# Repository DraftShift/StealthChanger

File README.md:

#  StealthChanger
**Tool changing system for Vorons and other front mount printer motion systems.**

&nbsp;&nbsp;&nbsp;&nbsp;&nbsp;&nbsp;
<a href="https://github.com/sponsors/DraftShift" target="_blank" alt="Sponsor Us">&color=rgb(191%2C%2057%2C%20137))</a>

 ## 🌐 Official Website

StealthChanger now has an official website!

👉 **https://stealthchanger.com** 

##

## Introduction

Unlike the name suggests we support more then just stealthburner.

Due to difficulties with heat insert and aligning of bearings and mounts we wanted to try a more simplistic design based on bushings and pins.

This is a very light design, requiring less parts and as such is cheaper and easier to build.  Input shaper tests have shown it to be as rigid if not more than current Tapchanger.

All parts are easily replaceable without reprinting if wear happens, life of the bushings and pins are still being tested.

## Tool compatability
Currently we support the standard Stealth Burner, Dragon Burner, Rapid Burner, Yavoth, AntHead, A4T, XOL, Jabberwocky and Archetype BlackBird.  There is also a usermod for the [Mini Stealth Burner](UserMods/jdmontgomer/MiniSB_SC).

## V1.1 Release
The original StealthChanger shuttle and backplates have been updated to V1.1, this update is to improve rigidity and probe accuracy. To help identify the version, "V1.1" has been clearly marked on all shuttles and backplates. please note, V1.1 is NOT compatible with previous versions. Updated documentation will follow shorly.

## Documentation and Info

Please use our [wiki](../../wiki) for more information and documentation.

- [Bill of Materials](../../wiki/Bill-of-Materials)
- [Docks](../../wiki/Docks)
- [Printing](../../wiki/Printing)
- [Assembling](../../wiki/Assembling)
- [Installation](../../wiki/Installation)
- [Configuration](../../wiki/Configuration)
- [Calibration](../../wiki/Calibration)
- [Slicers](../../wiki/Slicers)
- [Serials](../../wiki/Serials)
- [Support and FAQs](../../wiki/Support-and-FAQs)
- [Contributing & Donating](../../wiki/Contributing-and-Donating)
- [Team & Credits](../../wiki/Team-and-Credits)
- [Vendors & Kits](../../wiki/Vendors-and-Kits)

## Preview
### Explaination Video featuring GMBridge

### Printed Parts (Dragonburner) by BT123

### Important! - Check for clear Hex's (Dragonburner) by BT123

### Assembled Shuttle and Backplate by BT123

### Motion (Stealthburner) by TheSin-

### Docking (Stealthburner) by fiferboy

Originally based on Viesturz's [Tapchanger](https://github.com/viesturz/tapchanger)

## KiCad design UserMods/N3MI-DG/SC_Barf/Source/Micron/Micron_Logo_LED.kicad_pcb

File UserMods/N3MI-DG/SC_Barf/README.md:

# SC Barf LEDs

PCBs with 1.5mm RGB LEDs arranged into the StealthChanger logo pattern, both Voron and Micron styles.

## Example Config

```text
[neopixel rgb_logo]
pin: PB3
color_order: GRB
chain_count: 21 # 21 for Voron style, 19 for Micron style.
initial_RED: 0.3
initial_BLUE: 0.0
initial_GREEN: 0.3
```

## How to Order from JLCPCB

- Add Gerber zip file
- Select the PCB qty you want
- Select the PCB color you want
- Select `Order Number(Specify Position)`
- Enable PCB Assembly
- Select `Added by Customer` in the Tooling holes section
- Press the `Next` button
- Press the next `Next` button
- Add BOM file `BOM-JLC.csv`
- Add CPL file `CPL-JLC.csv`
- Click the `Process BOM & CPL` button
- Make sure the selected componants are correct
- Click the `Next` button
- Confirm componant placement
- Click the `Next` button
- Save to cart & checkout.

Note. there is an alternative RGB led componant that can be selected if the `SK6805-EC15` is out of stock. `DY-S1515065/RGBC/6805-5T` by TONYU is 1:1 compatible but the JLC footprint is rotated 180 degrees. Confirm you have the correct orientations.

### SK6805-EC15

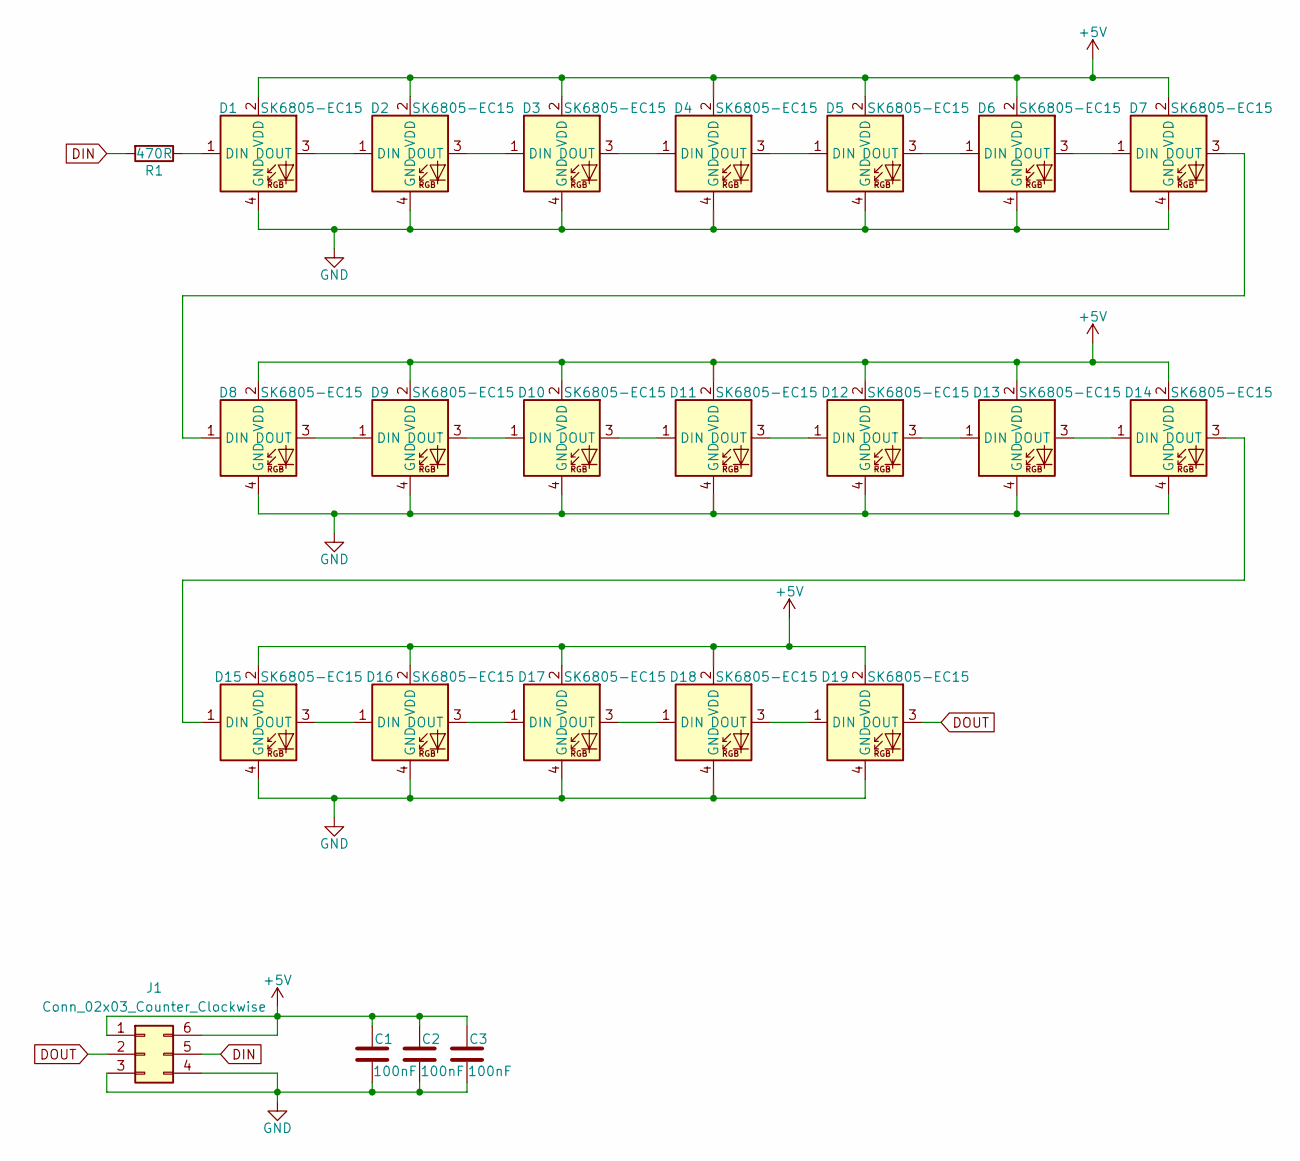
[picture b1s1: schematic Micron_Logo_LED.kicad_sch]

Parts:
C1, C2, C3: 100nF; C_0402_1005Metric; LCSC C14445
D1, D2, D3, D4, D5, D6, D7, D8, D9, D10, D11, D12, D13, D14, D15, D16, D17, D18, D19: SK6805-EC15; LCSC C2890035
J1: Conn_02x03_Counter_Clockwise; PinHeader_2x03_P2.54mm_Vertical_SMD
R1: 470R; R_0402_1005Metric; LCSC C25117

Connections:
+5V: C1.2, C2.2, C3.2, D1.2 (VDD), D2.2 (VDD), D3.2 (VDD), D4.2 (VDD), D5.2 (VDD), D6.2 (VDD), D7.2 (VDD), D8.2 (VDD), D9.2 (VDD), D10.2 (VDD), D11.2 (VDD), D12.2 (VDD), D13.2 (VDD), D14.2 (VDD), D15.2 (VDD), D16.2 (VDD), D17.2 (VDD), D18.2 (VDD), D19.2 (VDD), J1.1, J1.6
DIN: J1.5, R1.2
DOUT: D19.3 (DOUT), J1.2
GND: C1.1, C2.1, C3.1, D1.4 (GND), D2.4 (GND), D3.4 (GND), D4.4 (GND), D5.4 (GND), D6.4 (GND), D7.4 (GND), D8.4 (GND), D9.4 (GND), D10.4 (GND), D11.4 (GND), D12.4 (GND), D13.4 (GND), D14.4 (GND), D15.4 (GND), D16.4 (GND), D17.4 (GND), D18.4 (GND), D19.4 (GND), J1.3, J1.4
unnamed: D1.1 (DIN), R1.1
unnamed: D1.3 (DOUT), D2.1 (DIN)
unnamed: D2.3 (DOUT), D3.1 (DIN)
unnamed: D3.3 (DOUT), D4.1 (DIN)
unnamed: D4.3 (DOUT), D5.1 (DIN)
unnamed: D5.3 (DOUT), D6.1 (DIN)
unnamed: D6.3 (DOUT), D7.1 (DIN)
unnamed: D7.3 (DOUT), D8.1 (DIN)
unnamed: D8.3 (DOUT), D9.1 (DIN)
unnamed: D9.3 (DOUT), D10.1 (DIN)
unnamed: D10.3 (DOUT), D11.1 (DIN)
unnamed: D11.3 (DOUT), D12.1 (DIN)
unnamed: D12.3 (DOUT), D13.1 (DIN)
unnamed: D13.3 (DOUT), D14.1 (DIN)
unnamed: D14.3 (DOUT), D15.1 (DIN)
unnamed: D15.3 (DOUT), D16.1 (DIN)
unnamed: D16.3 (DOUT), D17.1 (DIN)
unnamed: D17.3 (DOUT), D18.1 (DIN)
unnamed: D18.3 (DOUT), D19.1 (DIN)

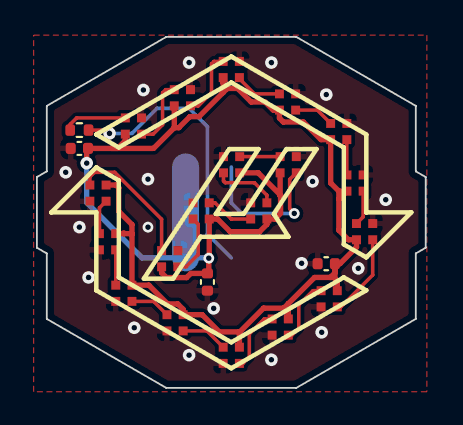
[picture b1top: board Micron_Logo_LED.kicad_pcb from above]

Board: 2 copper layers, 21.6 x 19.5 mm, 24 parts (1 on the bottom side), 23 nets.

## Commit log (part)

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2024-10-21 Fix link
2024-10-21 No need to move higher that is covered already
2024-10-21 Tweaking
2024-10-21 wording
2024-10-21 Update again
2024-10-21 Enumerate Dock steps
2024-10-21 Split the notes
2024-10-21 Use T0 not Tool 0
2024-10-21 Add notes about options steps
2024-10-21 Link paper test to klipper docs
2024-10-21 Break in all tools not just one
2024-10-21 Fix english
2024-10-21 update using wording from tap project
2024-10-21 Bold it as it's important
2024-10-21 Add +1 to park_z and flow table for dock/undock
2024-10-21 Fix typos
2024-10-21 Use sparse checkout
2024-10-21 Update tophat sizing
2024-10-21 Add TEST Docking commands
2024-10-22 Add TAP only to FAQ
2024-10-26 Add new switch mount
2024-10-29 SC Barf PCBs (#82)
    * Stealthchanger Barf LEDs
    * Update Readme
2024-10-29 Add images for all types
2024-10-29 Try to fix links?
2024-10-30 Since the klipper version of the paper test still uses automated tools which would redo the probing, lets write our own using the Klipper version as a ref
2024-10-30 Fix typo
2024-10-30 Add move to wipetower on tool change for prusa
2024-10-30 Reword
2024-10-30 Remove repeat sentence
2024-11-01 Update for NH2
2024-11-02 Maro was added before it was ready
2024-11-06 Change the recommended path to work with wiper
2024-11-12 Moving to new repo c path
2024-11-12 Moving to new repo
2024-11-13 Add switch arm for future use
2024-11-16 SC.076 Printing
2024-11-16 Added Image of SB Numer Cowel in Use (#85)
    * Add files via upload
    * SC.076 Printing
    * SC.076 Printing
    * SC.076 Printing
    * q
    * SC.076 Printing
2024-11-19 changed something
2024-11-19 Spacer for Anthead Sherpa-Mini extruder (#87)
    * Sherpa-mini spacer for Anthead
    Sherpa-mini spacer for Anthead
    * Update readme.md
    * changed something
2024-11-19 resubmit user mod folder (#88)
2024-11-23 Update for SC Barf
2024-11-27 Forgot to update A4T
2024-11-28 Add 0.05 more tolerance in the logo area
2024-11-29 Change up the Vendors page
2024-11-29 Move flag to after
2024-11-29 Add VorLong +100 Y
2024-11-29 Remove superfluous stl from the file name
2024-12-02 A4T / Xol fan splitter PCB initial commit
2024-12-14 Add missing gantry extrusions
2024-12-15 bullets
2024-12-15 done tn
2024-12-16 test
2024-12-20 Single Commit
2024-12-20 Single Commit (#92)
2024-12-28 StealthBurner SC Barf Version (#93)
2024-12-29 Initial Drop NH36 Mount Socks
2024-12-29 Update readme.md
    Content did not transfer over
2024-12-29 add p
2024-12-29 step file added
2025-01-02 Add logo publically
2025-01-03 Add numbered cowls 0-5 for Ant Head (#96)
    * Create readme.txt
    * Add files via upload
    * Update readme.txt
    update text description
    * Update readme.txt
2025-01-04 SC Build Plates from Discord User Project
2025-01-06 ANTHEAD NOZZLE LED FIX
    A simple modification of N3MI's original LED for the SF ANTHEAD. Main bodies are labeled VORON LOGO. LED's are labeled LED. You must split the LED to objects in slicer and orient correctly.
2025-01-06 Anthead nozzle led fix (#98)
    * ANTHEAD NOZZLE LED FIX
    A simple modification of N3MI's original LED for the SF ANTHEAD. Main bodies are labeled VORON LOGO. LED's are labeled LED. You must split the LED to objects in slicer and orient correctly.
    * Create ANTHEAD_NOZZLE_LED_FIXES.md
    * Update readme.md
2025-01-07 N3MI Anthead Mods (#99)
2025-01-23 Add Fysetc
2025-01-23 Add Vendors
2025-01-25 Link to secific checkout since it was removed recently
2025-01-26 Add a note about input shaper
2025-01-27 Former was repeated, no need
2025-01-27 Add Micron and Anthead to credits
2025-01-27 Add new header for the special mentions
2025-01-29 Updated instructions
2025-01-29 add extra docs to MiniBFI
2025-02-03 Add png versino of micron logo
2025-02-10 renamed original spacer and added another
    renamed sherpaminispacer to sherpaminispacerwithtab and added a variation sherpamininotab.
2025-02-10 renamed original spacer and added another (#102)
    renamed sherpaminispacer to sherpaminispacerwithtab and added a variation sherpamininotab.
2025-02-26 Spacer mod (#104)
    * renamed original spacer and added another
    renamed sherpaminispacer to sherpaminispacerwithtab and added a variation sherpamininotab.
    * Spacer mod for anthead to use orbiter
    Spacer for orbiter extruder bolt spacing.
2025-03-02 Fix Anthead backplate, was out by 1mm
2025-03-07 Update Bill-of-Materials.md
    Added a note about Xol / A4T compatibility
2025-03-07 Update Bill-of-Materials.md (#106)
    Added a note about Xol / A4T compatibility
2025-03-07 wiki-FAQ entry for short tools and z-rail-limits and update old xol readme (#107)
    * add Xol-Toolhead UserMod
    add Xol-Toolhead UserMod with dock
    * Update README_Xol-Toolhead.md
    * delete old folder due to rename and merge
    * Update README.md
    * add wiki entry for issue with short tools and z-rail-travel limit
2025-03-14 Updated Xol /A4T BOM (#109)
    * Update Bill-of-Materials.md
    Added a note about Xol / A4T compatibility
    * Update Bill-of-Materials.md
    * Update Bill-of-Materials.md
2025-03-14 add Fabreeko and add can bus listing to Fysetc
2025-03-14 Fix link, paste issue
2025-03-15 Update Bill-of-Materials.md (#110)
2025-03-18 UserMod for StealthChanger Skirts: initial commit
2025-03-18 UserMod Tavroswyn/Vorlong_+100y added: Initial Commit with Deck Panel as first modification
2025-03-18 UserMod Tavroswyn/Vorlong_+100y added: Initial Commit with Deck Panel as first modification (#112)
2025-03-28 Correction, Micron uses 19 LEDs
2025-04-02 Updated readme
    updated readme's
2025-04-02 Rename
    Rename
2025-04-03 Renamed files added new version
2025-04-03 Updates (#114)
    * Added Anthead Usermods
    Added Anthead usermods only for now.
    * Updated readme
    updated readme's
    * Update readme.md
    * Update Readme.md
2025-04-03 Im Dumb (#115)
    Removed duplicate files
2025-04-04 Added files
2025-04-04 Renamed some files
2025-04-04 Renamed a file.
2025-04-04 Added images
2025-05-14 N3MI endstop mount and brackets
2025-05-18 IllFilamentRunout
2025-05-18 add stealthburner beef backplate
    add stealthburner beef backplate
2025-06-14 Fix an issue with Anthead exports
2025-06-14 add usermod Stealthburner beef backplate (#123)
    add usermod Stealthburner beef backplate
2025-06-17 Waited long enough on the SV08, adding support
2025-06-29 feat: Set up Python testing infrastructure with Poetry and pytest
    - Initialize Poetry package manager with pyproject.toml
    - Add pytest, pytest-cov, and pytest-mock as dev dependencies
    - Configure pytest with markers for unit, integration, and slow tests
    - Set up coverage reporting with 80% threshold requirement
    - Create test directory structure with shared fixtures in conftest.py
    - Add Poetry scripts for running tests (both 'test' and 'tests' commands)
2025-07-18 Testing a layout for LDO kits/links
2025-07-26 Add Cartographer Endstop Mount
2025-07-27 Add CNC Shuttle Cartographer Mounts (#127)
2025-07-27 Fix a very small interference
2025-08-15 Initial Data Upload
2025-08-15 Update readme.md
    Added Images
2025-08-15 Added HF and UHF Variant
2025-08-17 UserMod Tavroswyn added PCB Mount for Anthead with Sherpa Mini and EBB36
2025-08-18 PCB36 Mounting System (Primarily EBB36) for Anthead and Sherpa Mini (#130)
    * Initial Data Upload
    * Create readme.md
    * Update readme.md
    * Update readme.md
    Added Images
    * Update readme.md
2025-08-21 Update Repo Location for per tool probe to current location
2025-08-31 Add Split Sock
2025-08-31 Renaming file
2025-09-09 Added Split Sock (#133)
    * Add Split Sock
    * Update readme.md
2025-09-15 the /p/ was removed but I missed that it went form product to products as well
2025-09-15 Thanks nic
2025-09-16 UsrMod_CHCB-V Mount initial comit
2025-10-03 Update README.md
    Toolhead list updated
2025-10-18 Add initial EBB36 v3.0 and Eddy Mount files
2025-10-18 Update Readme.md
    Fix paths
2025-10-21 Added Anthead SF WWG2 Setup and Rev 9 for Sherpa Mini
2025-10-21 Added additional readme
2025-10-21 Updated Images
2025-10-21 Replace images in readme with updated toolhead images
    Updated images in the readme to reflect new toolhead.
2025-10-21 Update Remove Images
2025-10-21 Fix image filename in readme
    Updated image filename in the readme for consistency.
2025-10-21 Fix model name in README for PCB Mount solution
    Updated the title to reflect the correct model name.
2025-10-21 Revise readme for Anthead Sherpa Mini EBB 36 PCB Mount
    Updated readme to reflect changes in revision 9, including fixes for torsion twist and enhancements for spring steel capturing.
2025-10-21 Clean up readme by removing duplicate images
    Removed duplicate images from the readme file.
2025-10-28 UsrMod Add CHCB-V HotEnd Mount For Anthead (#135)
    * UsrMod_CHCB-V Mount initial comit
    * UsrMod CHCB-V Fix
    * Update readme.md
    * Update readme.md
2025-10-29 Add initial readme and images
2025-10-29 Fix image paths
2025-10-29 Fix SHCS vs BHCS for M3x12
2025-10-29 Add image
2025-10-29 Change image size and fix another BH/SH issue
2025-10-30 Add low-profile PG7 mount for printed A motor to provide USB/CAN clearance in rear corner
2025-10-30 Updated file directory
2025-10-30 Add Jabberwocky SC backplates
2025-11-03 Add low-profile pg7 gantry mounts, images and update readmes
2025-11-03 Fix more image paths in readmes
2025-11-03 Fix orientantation
2025-11-03 Add low-profile pg7 mount companion modification to CNC shuttle mounts for Beacon/Carto (#138)
    * Add low-profile pg7 gantry mounts, images and update readmes
    * Fix image paths in Readme
    * Fix more image paths in readmes
    * Add additional verbiage explaining what this does
2025-11-06 Fix the ear placement as per Issue #140
2025-11-06 Fix broken link to PG7 at the bottom of CNC Shuttle Readme (#139)
    * Fix broken link to PG7 in Readme
2025-11-08 Add Fystec/LDO specific flag plates to account for screw spacing
2025-11-11 Add link to 1.1 in Readme
2025-11-11 Add png files and fix typos in Readme
2025-11-12 Update Readme to new install instructions and .cfg example
2025-11-12 Fix typo in Readme
2025-11-12 Add v1.1 and update v1.0 with ldo/fystec specific top plates (#142)
    * Add low-profile pg7 gantry mounts, images and update readmes
    * Fix image paths in Readme
    * Fix more image paths in readmes
    * Add additional verbiage explaining what this does
    * Fix broken link to PG7 in Readme
    * Fix broken link to PG7 in Readme
2025-11-17 Add usermod for backplate pcb
2025-11-17 Update README.md path to install to raw (#143)
    install path needs to be raw to ensure it will execute
2025-11-19 Formatting changes
2025-11-20 Addition of A4T CHCB-V toolhead
    Addition of A4T CHCB-V toolhead
2025-11-20 Revise readme for A4T Cowl to include Orbitor 2
    Updated readme to include Orbitor 2 mounting pattern support.
2025-11-23 add testing short mount with pcb moved to rear
2025-12-03 Monolith gantry and XY joints for Stealthchanger (#148)
    * Create read.me
    * Update and rename read.me to README.md
    * Update README.md
    * Update README.md
    * Update README.md
    * Update README.md
2025-12-03 Add usermod for backplate pcb (#145)
2025-12-03 A4T Toolhead for CHCB-V and Sherpa Mini Mounting Pattern (#147)
    * Initial Data Upload
    * Create readme.md
    * Update readme.md
    * Update readme.md
    Added Images
    * Update readme.md
2025-12-04 Updated to Improve Nozzle Location
2025-12-06 fix(docs): dead link in CONTRIBUTING.md
2025-12-06 mod(anthead): Add HGX-Lite Adaptor
2025-12-06 Add MF-SHROOM readme
2025-12-06 move to github username folder
2025-12-08 Fix right insert depth
2025-12-21 Usermod Tavroswyn: added TopHatAligner
2025-12-21 Usermod Tavroswyn Vorlong added Side Skirt modifications and picture
2025-12-27 Revert
2025-12-30 revert change to CONTRIBUTING.md
2025-12-31 Corrected naming issues
2026-01-17 Mark Z-Umbilical Alternative as deprecated
    Updated readme to indicate deprecation of the usermod.
    There is better options now days. I do not recommend my usermod anymore.
2026-01-17 Cleaning up duplicated Usermod
    Cleaning up duplicated Usermod
2026-02-22 Add more folders
2026-02-22 Add pictures
2026-02-22 Rename Pictures
2026-02-22 Fix image names
2026-02-23 Add more pictures.
